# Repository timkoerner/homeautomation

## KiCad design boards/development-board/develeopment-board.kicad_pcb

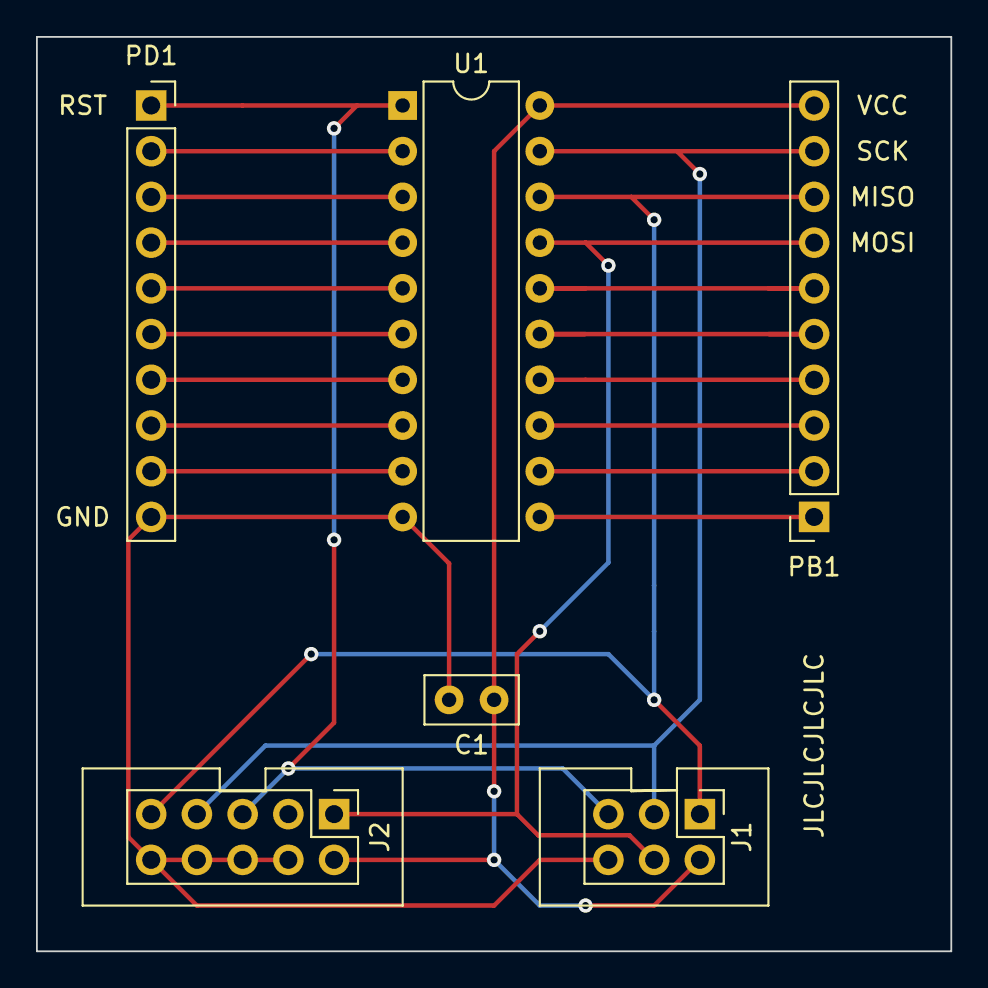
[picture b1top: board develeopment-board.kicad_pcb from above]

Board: 2 copper layers, 50.8 x 50.8 mm, 6 parts (0 on the bottom side), 20 nets.

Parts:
C1: 100nF; C_Disc_D5.0mm_W2.5mm_P2.50mm
J1: AVR-ISP-6; PinHeader_2x03_P2.54mm_Vertical
J2: AVR-ISP-10; PinHeader_2x05_P2.54mm_Vertical
PB1: Conn_01x10; PinSocket_1x10_P2.54mm_Vertical
PD1: Conn_01x10; PinSocket_1x10_P2.54mm_Vertical
U1: ATtiny2313-20PU; DIP-20_W7.62mm

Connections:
unnamed: C1.1, J1.2, J2.2, PB1.10, U1.20
unnamed: C1.2, J1.6, J2.4, J2.6, J2.8, J2.10, PD1.10, U1.10
unnamed: J1.1, J2.9, PB1.8, U1.18
unnamed: J1.3, J2.7, PB1.9, U1.19
unnamed: J1.4, J2.1, PB1.7, U1.17
unnamed: J1.5, J2.5, PD1.1, U1.1
unnamed: PB1.1, U1.11
unnamed: PB1.2, U1.12
unnamed: PB1.3, U1.13
unnamed: PB1.4, U1.14
unnamed: PB1.5, U1.15
unnamed: PB1.6, U1.16
unnamed: PD1.2, U1.2
unnamed: PD1.3, U1.3
unnamed: PD1.4, U1.4
unnamed: PD1.5, U1.5
unnamed: PD1.6, U1.6
unnamed: PD1.7, U1.7
unnamed: PD1.8, U1.8
unnamed: PD1.9, U1.9

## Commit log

2021-01-03 project creation
2021-01-03 update gradle version
2021-01-03 add main activity
2021-01-03 add navigation dependency
2021-01-03 add material dependency
2021-01-03 setup main layout
2021-01-03 use viewbinding
2021-01-03 add color scheme
2021-01-03 add window fragment using viewmodel
2021-01-03 fix color scheme
2021-01-03 fix navigation component
2021-01-03 add firebase dependency
2021-01-04 add simple test
2021-01-04 create development board
2021-01-07 create recycler for window info
